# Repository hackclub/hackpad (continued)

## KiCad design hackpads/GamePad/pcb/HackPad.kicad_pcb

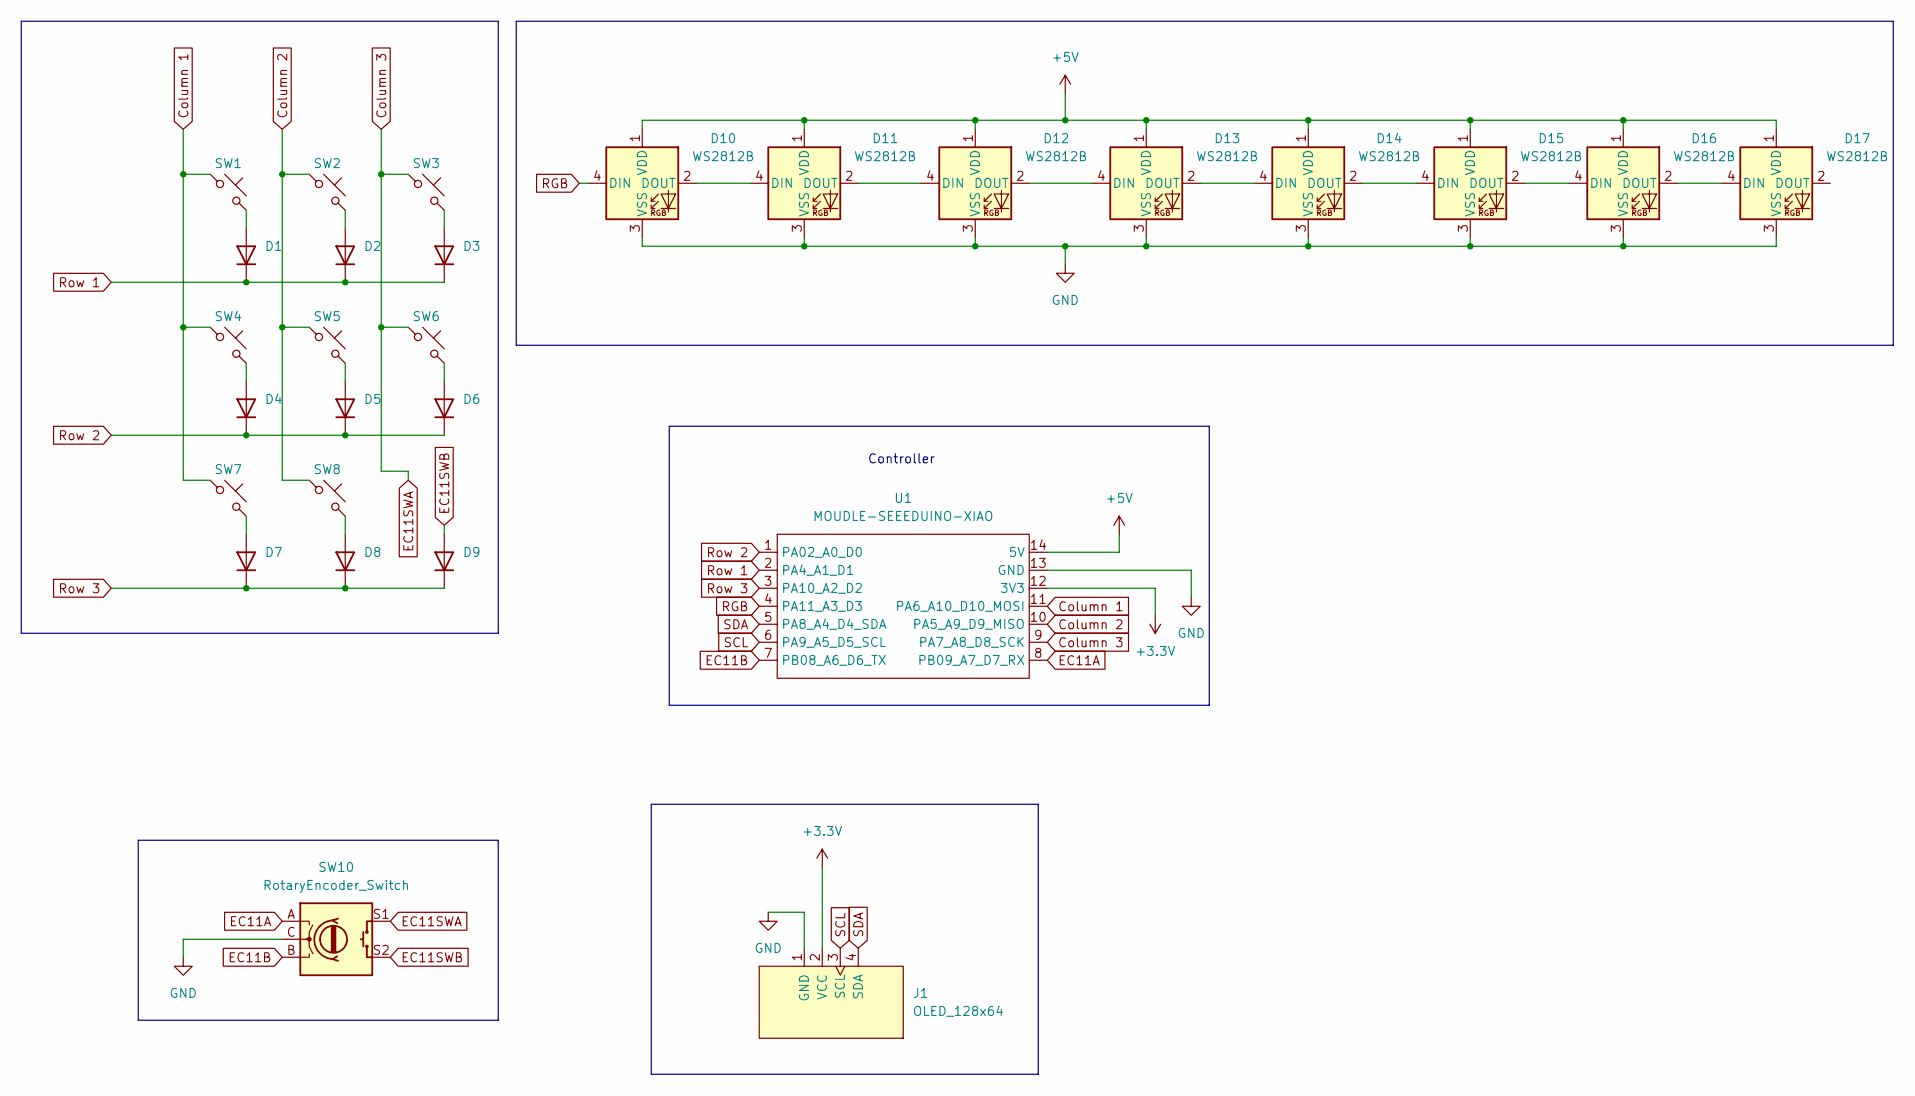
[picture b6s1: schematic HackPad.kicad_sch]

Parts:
D1, D2, D3, D4, D5, D6, D7, D8, D9: D; Diode_DO-35
D10, D11, D12, D13, D14, D15, D16, D17: WS2812B; LED_WS2812B
J1: OLED_128x64
SW1, SW2, SW3, SW4, SW5, SW6, SW7, SW8: SW_Push_45deg; MX_PCB_1.00u
SW10: RotaryEncoder_Switch; RotaryEncoder_Alps_EC11E-Switch_Vertical_H20mm
U1: MOUDLE-SEEEDUINO-XIAO; XIAO-Generic-Hybrid-14P-2.54-21X17.8MM

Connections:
+3.3V: J1.2 (VCC), U1.12 (3V3)
+5V: D10.1 (VDD), D11.1 (VDD), D12.1 (VDD), D13.1 (VDD), D14.1 (VDD), D15.1 (VDD), D16.1 (VDD), D17.1 (VDD), U1.14 (5V)
Column 1: SW1.1, SW4.1, SW7.1, U1.11 (PA6_A10_D10_MOSI)
Column 2: SW2.1, SW5.1, SW8.1, U1.10 (PA5_A9_D9_MISO)
Column 3: SW3.1, SW6.1, SW10.S1, U1.9 (PA7_A8_D8_SCK)
EC11A: SW10.A, U1.8 (PB09_A7_D7_RX)
EC11B: SW10.B, U1.7 (PB08_A6_D6_TX)
EC11SWB: D9.2 (A), SW10.S2
GND: D10.3 (VSS), D11.3 (VSS), D12.3 (VSS), D13.3 (VSS), D14.3 (VSS), D15.3 (VSS), D16.3 (VSS), D17.3 (VSS), J1.1 (GND), SW10.C, U1.13 (GND)
unnamed: D1.2 (A), SW1.2
unnamed: D2.2 (A), SW2.2
unnamed: D3.2 (A), SW3.2
unnamed: D4.2 (A), SW4.2
unnamed: D5.2 (A), SW5.2
unnamed: D6.2 (A), SW6.2
unnamed: D7.2 (A), SW7.2
unnamed: D8.2 (A), SW8.2
unnamed: D10.2 (DOUT), D11.4 (DIN)
unnamed: D11.2 (DOUT), D12.4 (DIN)
unnamed: D12.2 (DOUT), D13.4 (DIN)
unnamed: D13.2 (DOUT), D14.4 (DIN)
unnamed: D14.2 (DOUT), D15.4 (DIN)
unnamed: D15.2 (DOUT), D16.4 (DIN)
unnamed: D16.2 (DOUT), D17.4 (DIN)
RGB: D10.4 (DIN), U1.4 (PA11_A3_D3)
Row 1: D1.1 (K), D2.1 (K), D3.1 (K), U1.2 (PA4_A1_D1)
Row 2: D4.1 (K), D5.1 (K), D6.1 (K), U1.1 (PA02_A0_D0)
Row 3: D7.1 (K), D8.1 (K), D9.1 (K), U1.3 (PA10_A2_D2)
SCL: J1.3 (SCL), U1.6 (PA9_A5_D5_SCL)
SDA: J1.4 (SDA), U1.5 (PA8_A4_D4_SDA)

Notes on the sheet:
Controller

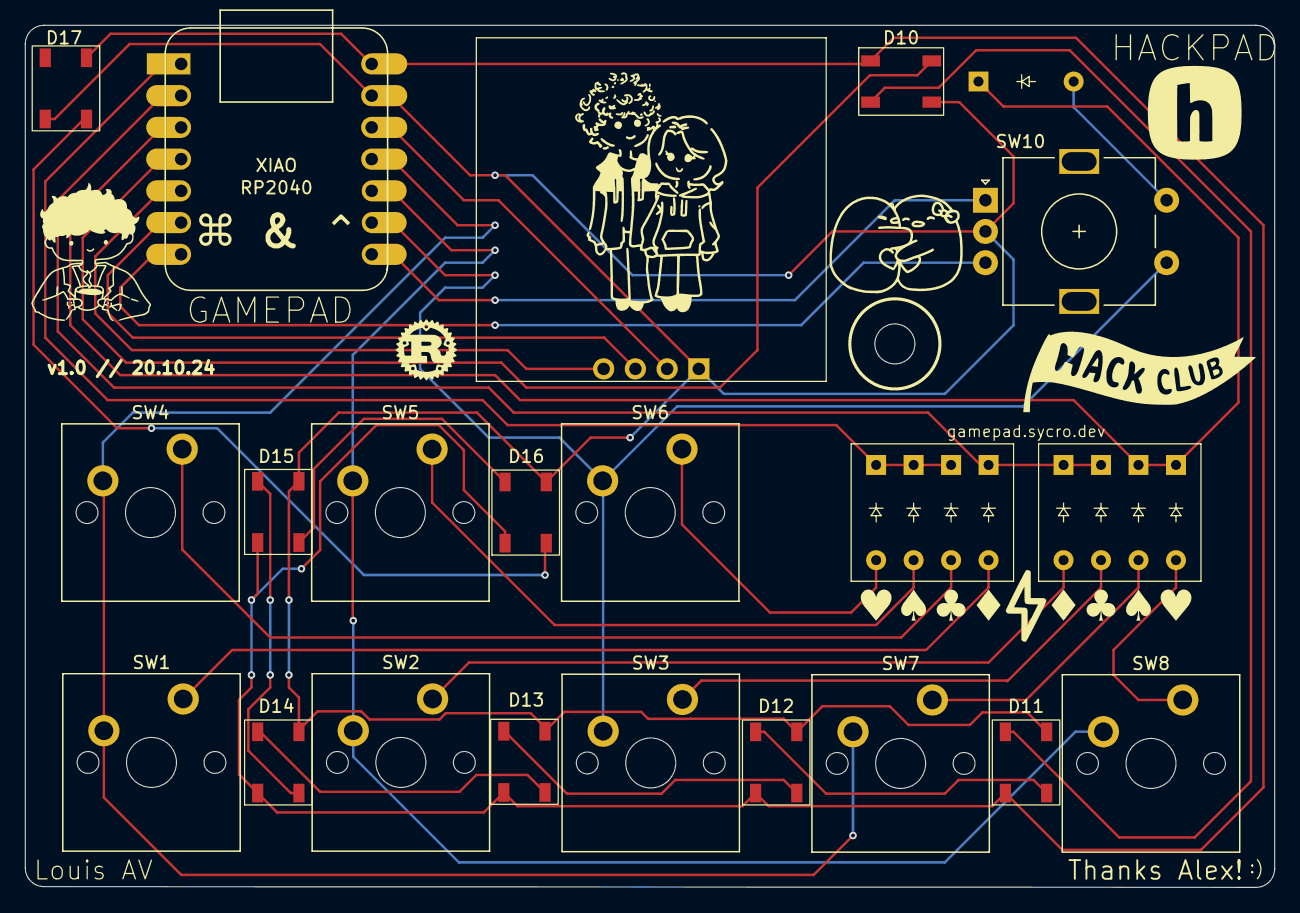
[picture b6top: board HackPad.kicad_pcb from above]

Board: 2 copper layers, 100.0 x 69.0 mm, 28 parts (0 on the bottom side), 30 nets.
